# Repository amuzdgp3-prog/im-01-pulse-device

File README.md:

# ИМ-01 — устройство учёта импульсов для игровых аппаратов

Отдельный модуль к системе обслуживания аппаратов `2.apixspb.ru`. Устройство слушает импульсные
выходы монетоприёмника и купюроприёмника, копит показания в FRAM и дважды в сутки передаёт их на
сервер по LTE Cat.1. Показания идут **параллельно** ручным и в финансовую историю не пишутся.

Полное задание и спецификация: [docs/IM-01_FULL_BRIEF.md](docs/IM-01_FULL_BRIEF.md).

## Где что лежит

| Папка | Что там |
| --- | --- |
| `docs/` | задание, отчёты по шагам проверки, графики |
| `sim/` | аналоговая симуляция (ngspice): схемы, прогонщик, сводка результатов |
| `firmware/` | прошивка MCU (шаг 3, пока пусто) |
| `hardware/` | проект KiCad (шаг 5, пока пусто) |
| `server-contract/` | заметки по серверной части; сама реализация — в репозитории `2.apixspb.ru` (шаг 2) |

## Состояние по плану проверки (§9)

| Шаг | Что | Статус |
| --- | --- | --- |
| 1 | Аналоговая симуляция | **сделан** — [отчёт](docs/step1-analog-sim.md); виртуальная модель всего устройства — `sim/run_final.py` |
| 2 | Серверная часть в `2.apixspb.ru` | отложена владельцем: сначала железо |
| 3 | Прошивка в Renode | не начат |
| 4 | Сквозная проверка | не начат |
| 5 | Плата в KiCad | **сделана** — [описание](docs/hardware.md), файлы для JLCPCB в `hardware/fab/`; нужно ревью инженером перед заказом |

Перечень комплектующих с ценами LCSC и в РФ: [docs/ИМ-01_перечень_комплектующих.xlsx](docs/ИМ-01_перечень_комплектующих.xlsx).

## Как повторить симуляцию

```bash
sudo apt-get install -y ngspice
python3 sim/run_sim.py        # ~1 минута; matplotlib — по желанию, для графиков
```

Результат — `sim/results_auto.md` и графики в `sim/out/`.

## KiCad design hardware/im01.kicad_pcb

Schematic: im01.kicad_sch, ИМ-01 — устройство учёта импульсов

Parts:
C1: 47uF/50V; CP_Elec_6.3x7.7; MPN RVT1H470M0607; LCSC C970679
C2, C3: 4.7uF; C_1206_3216Metric; MPN 1206B475K500NT; LCSC C29823
C4, C5, C11, C18, C19, C20, C21, C22, C23, C24, C30, C34, C35: 100nF; C_0603_1608Metric; MPN CC0603KRX7R9BB104; LCSC C14663
C6, C7, C10: 22uF; C_1206_3216Metric; MPN CL31B226KPHNNNE; LCSC C87996
C8, C9, C14, C33: 470uF/6.3V; CP_Elec_6.3x7.7; MPN MA6.3V470M6X8; LCSC C54321567
C12, C25, C26, C27: 33pF; C_0402_1005Metric; MPN 0402CG330J500NT; LCSC C1562
C13: 10pF; C_0402_1005Metric; MPN CL05C100JB5NNNC; LCSC C32949
C15, C16: 1uF; C_0603_1608Metric; MPN CL10A105KB8NNNC; LCSC C15849
C17: 10uF; C_0805_2012Metric; MPN CL21A106KAYNNNE; LCSC C15850
C28, C29: 10pF; C_0402_1005Metric; MPN CL05C100JB5NNNC; LCSC C32949; not fitted
C31: 3.9pF; C_0402_1005Metric; MPN 0402CG3R9C500NT; LCSC C1566
C32: 1.8pF; C_0402_1005Metric; MPN 0402CG1R8C500NT; LCSC C1553
D1, D3: SS36; D_SMA; MPN SS36; LCSC C16015
D2: SMBJ33A; D_SMB; MPN SMBJ33A; LCSC C353366
D4: SMAZ5V1; D_SMA; MPN SMAZ5V1-13-F; LCSC C154748
D5: BAT54WS; D_SOD-323; MPN BAT54WS; LCSC C3040452
D6, D7, D8, D9: 1N4148W; D_SOD-123; MPN 1N4148W; LCSC C81598
D10: зелёный; LED_0805_2012Metric; MPN NCD0805G1; LCSC C84260
D11: красный; LED_0805_2012Metric; MPN NCD0805R1; LCSC C84256
F1: 0.5A/60V; Fuse_1812_4532Metric; MPN mSMD050-60V; LCSC C70113
H1, H2, H3, H4: M3; MountingHole_3.2mm_M3_Pad_Via
J1: ПИТАНИЕ 9-30В; JST_VH_B2P-VH_1x02_P3.96mm_Vertical; MPN B2P-VH(LF)(SN); LCSC C160315
J2: COIN; JST_XH_B2B-XH-A_1x02_P2.50mm_Vertical; MPN B2B-XH-A(LF)(SN); LCSC C158012
J3: BILL; JST_XH_B3B-XH-A_1x03_P2.50mm_Vertical; MPN B3B-XH-A(LF)(SN); LCSC C144394
J4: NANO SIM; SIM-SMD_NANO-SIM-XG6P-H1.35; MPN NANO SIM XG6P H1.35; LCSC C7529386
J5: U.FL; U.FL_Hirose_U.FL-R-SMT-1_Vertical; MPN U.FL-R-SMT-1(80); LCSC C88374
J6: SWD; Tag-Connect_TC2030-IDC-NL_2x03_P1.27mm_Vertical
L1: 10uH; IND-SMD_L7.3-W6.6_MHCI06030; MPN SLO0630H100MTT; LCSC C207842
Q1, Q2: 2N7002; SOT-23; MPN 2N7002; LCSC C8545
R1: 270k; R_0603_1608Metric; MPN 0603WAF2703T5E; LCSC C22965
R2: 49.9k; R_0603_1608Metric; MPN 0603WAF4992T5E; LCSC C23184
R3, R4: 41.2k; R_0603_1608Metric; MPN 0603WAF4122T5E; LCSC C23166
R5, R7, R10, R13, R16, R22, R29: 10k; R_0603_1608Metric; MPN 0603WAF1002T5E; LCSC C25804
R6, R19, R21: 100k; R_0603_1608Metric; MPN 0603WAF1003T5E; LCSC C25803
R11, R14: 2.2k; R_1206_3216Metric; MPN 1206W4F2201T5E; LCSC C17948
R12, R15: 4.7k; R_0603_1608Metric; MPN 0603WAF4701T5E; LCSC C23162
R18, R20, R27, R28: 1k; R_0603_1608Metric; MPN 0603WAF1001T5E; LCSC C21190
R23, R24, R25: 22Ω; R_0603_1608Metric; MPN 0603WAF220JT5E; LCSC C23345
R26: 0Ω; R_0402_1005Metric; MPN 0402WGF0000TCE; LCSC C17168
R30: 15k; R_0603_1608Metric; MPN 0603WAF1502T5E; LCSC C22809
SW1: ВЫГРУЗКА; SW-SMD_4P-L5.1-W5.1-P3.70-LS6.5-TL_H1.5; MPN TS-1187A-B-A-B; LCSC C318884
TP1: VIN; TestPoint_Pad_D1.0mm
TP2: VBAT; TestPoint_Pad_D1.0mm
TP3: +3V3; TestPoint_Pad_D1.0mm
TP4: GND; TestPoint_Pad_D1.0mm
TP5: MCU_DBG_TX; TestPoint_Pad_D1.0mm
TP6: MCU_DBG_RX; TestPoint_Pad_D1.0mm
TP9: USB_DP; TestPoint_Pad_D1.0mm
TP10: USB_DN; TestPoint_Pad_D1.0mm
TP11: VBUS; TestPoint_Pad_D1.0mm
TP12: USB_BOOT; TestPoint_Pad_D1.0mm
TP13: NET_STATUS; TestPoint_Pad_D1.0mm
U1: LMR16020; SOIC-8_L4.9-W3.9-P1.27-LS6.0-BL-EP; MPN LMR16020PDDAR; LCSC C190006
U2: ME6211C33; SOT-23-5; MPN ME6211C33M5G-N; LCSC C82942
U3: STM32G030K8T6; LQFP-32_7x7mm_P0.8mm; MPN STM32G030K8T6TR; LCSC C724044
U4: FM25L16B; SOIC-8_3.9x4.9mm_P1.27mm; MPN FM25L16B-GTR; LCSC C466849
U5, U6: EL817S1(B); SOP-4_L6.5-W4.6-P2.54-LS10.2-TL; MPN EL817S1(B)(TU)-F; LCSC C63268
U7: EG800K-EU; LGA-109_L17.7-W15.8-AIR780E; MPN EG800KEULC-I03-SNNSA; LCSC C44008839
U8: SRV05-4; SOT-23-6; MPN SRV05-4; LCSC C2836319
U9: TXS0102; VSSOP-8_2.3x2mm_P0.5mm; MPN TXS0102DCUR; LCSC C53434

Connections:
+3V3: C16.1, C17.1, C18.1, C21.1, C35.1, J6.1 (VCC), R10.1, R12.1, R15.1, R29.1, TP3.1, U2.5 (V_{OUT}), U3.4 (VDD), U4.3 (~WP), U4.7 (~HOLD), U4.8 (VDD), U9.7 (VCCB)
ANT_MOD: C28.1, R26.1, U7.35 (ANT_MAIN)
ANT_OUT: C29.1, J5.1 (In), R26.2
BILL_IN: C23.1, R16.2, U3.14 (PA7), U3.20 (PC6)
BILL_LA: D8.1 (K), D9.1 (K), U6.1 (AN)
BILL_OC: R15.2, R16.1, U6.4 (COL)
BILL_PULSE: D9.2 (A), J3.2, U6.2 (CAT)
BILL_R: D8.2 (A), R14.2
BILL_V12: J3.1, R14.1
BOOT: C5.1, U1.1 (BOOT)
BTN: C30.1, R29.2, SW1.1 (A), U3.32 (PB8)
COIN_IN: C22.1, R13.2, U3.13 (PA6), U3.18 (PA8)
COIN_LA: D6.1 (K), D7.1 (K), U5.1 (AN)
COIN_OC: R12.2, R13.1, U5.4 (COL)
COIN_PULSE: D7.2 (A), J2.2, U5.2 (CAT)
COIN_R: D6.2 (A), R11.2
COIN_V12: J2.1, R11.1
EN: R1.2, R2.1, U1.3 (EN)
FB: R4.2, R5.1, U1.5 (FB)
FRAM_CS: R10.2, U3.26 (PA15), U4.1 (~CS)
GND: C1.2, C2.2, C3.2, C4.2, C6.2, C7.2, C8.2, C9.2, C10.2, C11.2, C12.2, C13.2, C14.2, C15.2, C16.2, C17.2, C18.2, C19.2, C20.2, C21.2, C22.2, C23.2, C24.2, C25.2, C26.2, C27.2, C28.2, C29.2, C30.2, C31.2, C32.2, C33.2, C34.2, C35.2, D2.2 (A), D3.2 (A), D4.2 (A), D10.1 (K), D11.1 (K), H1.1, H2.1, H3.1, H4.1, J1.2, J4.5 (GND), J4.8 (GND), J4.9 (GND), J4.10 (GND), J4.11 (GND), J5.2 (Ext), J6.5 (GND), Q1.2 (S), Q2.2 (S), R2.2, R3.2, R5.2, R7.2, R19.2, R21.2, SW1.4 (D), TP4.1, U1.7 (GND), U1.9 (EP), U2.2 (V_{SS}), U3.5 (VSS), U4.4 (VSS), U5.3 (EM), U6.3 (EM), U7.1 (GND), U7.10 (GND), U7.27 (GND), U7.34 (GND), U7.36 (GND), U7.37 (GND), U7.40 (GND), U7.41 (GND), U7.45 (GND), U7.46 (GND), U7.47 (GND), U7.48 (GND), U7.70 (GND), U7.71 (GND), U7.72 (GND), U7.73 (GND), U7.88 (GND), U7.89 (GND), U7.90 (GND), U7.91 (GND), U7.92 (GND), U7.93 (GND), U7.94 (GND), U7.95 (GND), U8.2 (VN), U9.2 (GND)
LED1_A: D10.2 (A), R27.2
LED2_A: D11.2 (A), R28.2
LED_PULSE: R27.1, U3.30 (PB6)
LED_STATUS: R28.1, U3.31 (PB7)
MCU_DBG_RX: TP6.1, U3.23 (PA10/PA12)
MCU_DBG_TX: TP5.1, U3.22 (PA9/PA11)
MCU_RX: U3.10 (PA3), U9.1 (B2)
MCU_TX: U3.9 (PA2), U9.8 (B1)
MODEM_PWRKEY: Q1.3 (D), U7.7 (PWRKEY)
MODEM_RESET_N: Q2.3 (D), U7.15 (RESET_N)
MODEM_RXD: U7.17 (MAIN_RXD), U9.5 (A1)
MODEM_TXD: U7.18 (MAIN_TXD), U9.4 (A2)
NET_STATUS: TP13.1, U7.16 (NET_STATUS)
NRST: C20.1, J6.3 (~RESET), U3.6 (NRST)
PWRKEY_CTL: R18.1, U3.15 (PB0)
PWRKEY_G: Q1.1 (G), R18.2, R19.1
RESET_CTL: R20.1, U3.16 (PB1)
RESET_G: Q2.1 (G), R20.2, R21.1
RT: R3.1, U1.4 (RT/SYNC)
SIM_CLK: C27.1, J4.3 (CLK), R25.2, U8.4 (IO3)
SIM_CLK_M: R25.1, U7.13 (USIM1_CLK)
SIM_DATA: C25.1, J4.7 (I/O), R23.2, R30.2, U8.1 (IO1)
SIM_DATA_M: R23.1, U7.11 (USIM1_DATA)
SIM_RST: C26.1, J4.2 (RST), R24.2, U8.3 (IO2)
SIM_RST_M: R24.1, U7.12 (USIM1_RST)
SIM_VDD: C24.1, J4.1 (VCC), R30.1, U7.14 (USIM1_VDD), U8.5 (VP)
SPI_MISO: U3.28 (PB4), U4.2 (SO)
SPI_MOSI: U3.29 (PB5), U4.5 (SI)
SPI_SCK: U3.27 (PB3), U4.6 (SCK)
SW: C5.2, D3.1 (K), L1.1, U1.8 (SW)
SWCLK: J6.4 (SWCLK), U3.25 (PA14)
SWDIO: J6.2 (SWDIO), U3.24 (PA13)
USB_BOOT: TP12.1, U7.82 (USB_BOOT/KP_MKOUT[4])
USB_DN: TP10.1, U7.60 (USB_DM)
USB_DP: TP9.1, U7.59 (USB_DP)
VBAT: C6.1, C7.1, C8.1, C9.1, C10.1, C11.1, C12.1, C13.1, C31.1, C32.1, C33.1, D4.1 (K), D5.2 (A), L1.2, R4.1, TP2.1, U7.42 (VBAT), U7.43 (VBAT)
VBUS: TP11.1, U7.61 (USB_VBUS)
VDDEXT_SENSE: R22.2, U3.17 (PB2)
VDD_EXT: C34.1, R22.1, U7.24 (VDD_EXT), U9.3 (VCCA), U9.6 (OE)
VIN: C1.1, C2.1, C3.1, C4.1, D1.1 (K), D2.1 (K), R1.1, TP1.1, U1.2 (VIN)
VIN_CONN: F1.1, J1.1
VIN_F: D1.2 (A), F1.2, R6.1
VMCU_IN: C14.1, C15.1, D5.1 (K), U2.1 (V_{IN}), U2.3 (CE)
VSENSE: C19.1, R6.2, R7.1, U3.7 (PA0)

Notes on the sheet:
Вход питания 9–30 В
Преобразователь VBAT 3.84 В
Питание MCU и FRAM
MCU STM32G030K8
FRAM
Вход COIN
Вход BILL
Модем LTE Cat.1 bis
SIM-карта
Антенна
Индикация и кнопка
Отладка и крепёж
Флажки питания (ERC)

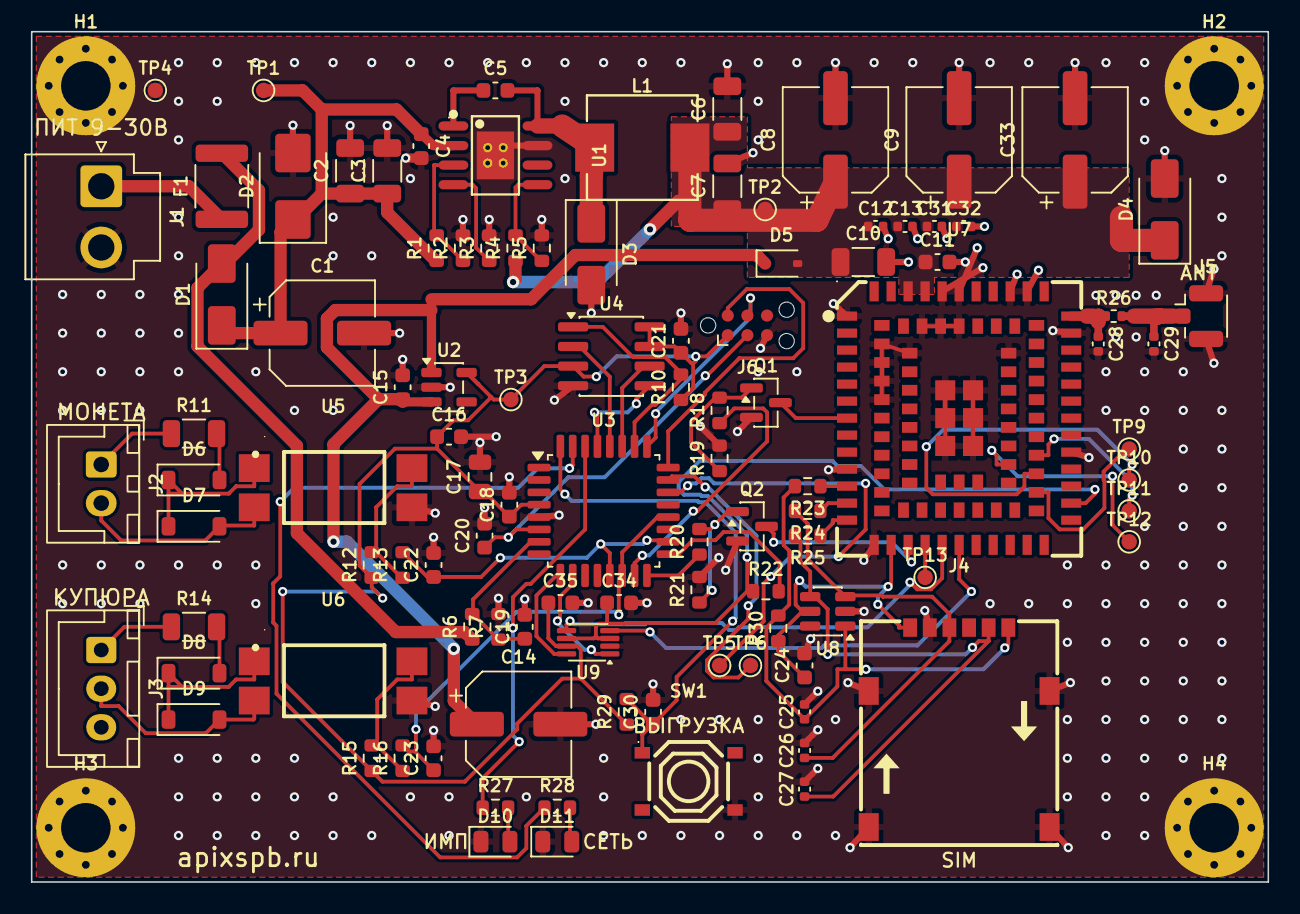
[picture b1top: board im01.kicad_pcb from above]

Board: 2 copper layers, 80.0 x 55.0 mm, 108 parts (0 on the bottom side), 65 nets.

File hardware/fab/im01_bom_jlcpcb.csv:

Comment,Designator,Footprint,LCSC Part #
B2P-VH(LF)(SN),J1,JST_VH_B2P-VH_1x02_P3.96mm_Vertical,C160315
0.5A/60V,F1,Fuse_1812_4532Metric,C70113
SS36,"D1,D3",D_SMA,C16015
SMBJ33A,D2,D_SMB,C353366
47uF/50V,C1,CP_Elec_6.3x7.7,C970679
4.7uF,"C2,C3",C_1206_3216Metric,C29823
100k,"R6,R19,R21",R_0603_1608Metric,C25803
10k,"R5,R7,R10,R13,R16,R22,R29",R_0603_1608Metric,C25804
100nF,"C4,C5,C11,C18,C19,C20,C21,C22,C23,C24,C30,C34,C35",C_0603_1608Metric,C14663
LMR16020PDDAR,U1,SOIC-8_L4.9-W3.9-P1.27-LS6.0-BL-EP,C190006
270k,R1,R_0603_1608Metric,C22965
49.9k,R2,R_0603_1608Metric,C23184
41.2k,"R3,R4",R_0603_1608Metric,C23166
10uH,L1,IND-SMD_L7.3-W6.6_MHCI06030,C207842
22uF,"C6,C7,C10",C_1206_3216Metric,C87996
470uF/6.3V,"C8,C9,C14,C33",CP_Elec_6.3x7.7,C54321567
SMAZ5V1,D4,D_SMA,C154748
BAT54WS,D5,D_SOD-323,C3040452
1uF,"C15,C16",C_0603_1608Metric,C15849
ME6211C33M5G-N,U2,SOT-23-5,C82942
STM32G030K8T6TR,U3,LQFP-32_7x7mm_P0.8mm,C724044
10uF,C17,C_0805_2012Metric,C15850
FM25L16B-GTR,U4,SOIC-8_3.9x4.9mm_P1.27mm,C466849
B2B-XH-A(LF)(SN),J2,JST_XH_B2B-XH-A_1x02_P2.50mm_Vertical,C158012
2.2k,"R11,R14",R_1206_3216Metric,C17948
1N4148W,"D6,D7,D8,D9",D_SOD-123,C81598
EL817S1(B)(TU)-F,"U5,U6",SOP-4_L6.5-W4.6-P2.54-LS10.2-TL,C63268
4.7k,"R12,R15",R_0603_1608Metric,C23162
B3B-XH-A(LF)(SN),J3,JST_XH_B3B-XH-A_1x03_P2.50mm_Vertical,C144394
EG800KEULC-I03-SNNSA,U7,LGA-109_L17.7-W15.8-AIR780E,C44008839
33pF,"C12,C25,C26,C27",C_0402_1005Metric,C1562
10pF,C13,C_0402_1005Metric,C32949
3.9pF,C31,C_0402_1005Metric,C1566
1.8pF,C32,C_0402_1005Metric,C1553
TXS0102DCUR,U9,VSSOP-8_2.3x2mm_P0.5mm,C53434
2N7002,"Q1,Q2",SOT-23,C8545
1k,"R18,R20,R27,R28",R_0603_1608Metric,C21190
NANO SIM XG6P H1.35,J4,SIM-SMD_NANO-SIM-XG6P-H1.35,C7529386
22Ω,"R23,R24,R25",R_0603_1608Metric,C23345
15k,R30,R_0603_1608Metric,C22809
SRV05-4,U8,SOT-23-6,C2836319
0Ω,R26,R_0402_1005Metric,C17168
U.FL-R-SMT-1(80),J5,U.FL_Hirose_U.FL-R-SMT-1_Vertical,C88374
зелёный,D10,LED_0805_2012Metric,C84260
красный,D11,LED_0805_2012Metric,C84256
TS-1187A-B-A-B,SW1,SW-SMD_4P-L5.1-W5.1-P3.70-LS6.5-TL_H1.5,C318884

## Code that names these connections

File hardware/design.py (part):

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B = "MCU STM32G030K8"
add(Part("U3", "STM32G030K8T6", "MCU_ST_STM32G0:STM32G030K8Tx", "Package_QFP:LQFP-32_7x7mm_P0.8mm", {
    "1": None, "2": None, "3": None, "4": "+3V3", "5": "GND", "6": "NRST",
    "7": "VSENSE",          # PA0  ADC1_IN0
    "8": None,
    "9": "MCU_TX",          # PA2  USART2_TX
    "10": "MCU_RX",         # PA3  USART2_RX
    "11": None, "12": None,
    "13": "COIN_IN",        # PA6  TIM16_CH1 — захват фронтов (DMA)
    "14": "BILL_IN",        # PA7  TIM17_CH1 — захват фронтов (DMA)
    "15": "PWRKEY_CTL",     # PB0
    "16": "RESET_CTL",      # PB1
    "17": "VDDEXT_SENSE",   # PB2
    "18": "COIN_IN",        # PA8  TIM1_CH1 — аппаратный счётчик фронтов
    "19": None,
    "20": "BILL_IN",        # PC6  TIM3_CH1 — аппаратный счётчик фронтов
    "21": None,
    "22": "MCU_DBG_TX",     # PA9  USART1_TX
    "23": "MCU_DBG_RX",     # PA10 USART1_RX
    "24": "SWDIO", "25": "SWCLK",
    "26": "FRAM_CS",        # PA15 SPI1_NSS
    "27": "SPI_SCK",        # PB3
    "28": "SPI_MISO",       # PB4
    "29": "SPI_MOSI",       # PB5
    "30": "LED_PULSE",      # PB6
    "31": "LED_STATUS",     # PB7
    "32": "BTN",            # PB8
}, "C724044", "STM32G030K8T6TR", B))
C("C17", "10uF", "+3V3", "GND", B)
C("C18", "100nF", "+3V3", "GND", B, note="у вывода VDD")
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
